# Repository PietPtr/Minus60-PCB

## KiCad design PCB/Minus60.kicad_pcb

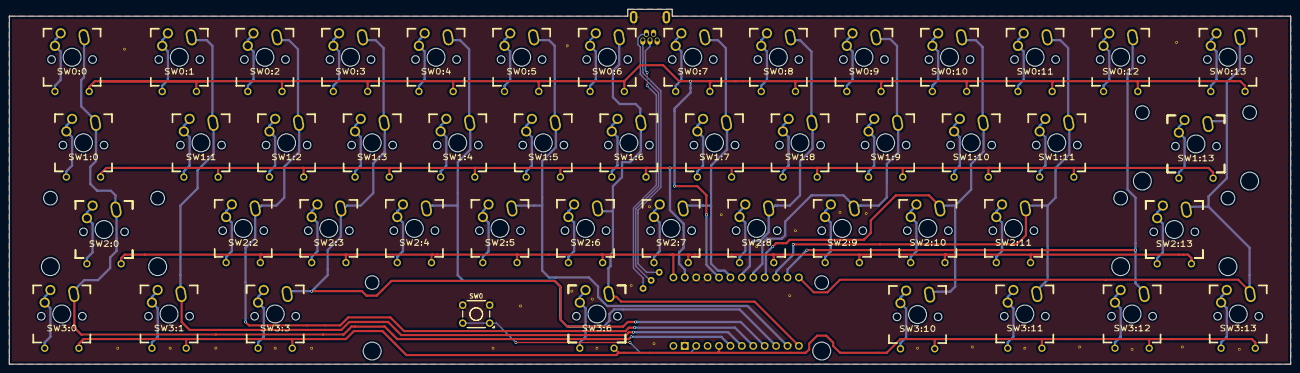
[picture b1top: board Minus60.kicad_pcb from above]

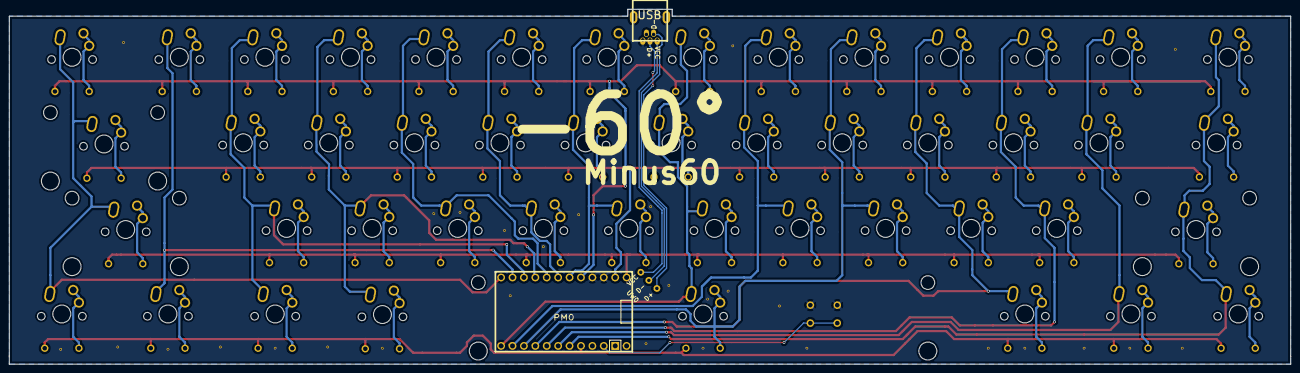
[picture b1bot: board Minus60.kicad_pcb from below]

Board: 2 copper layers, 285.2 x 79.0 mm, 51 parts (2 on the bottom side), 23 nets.

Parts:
P0: USB; USBMINI
PM0: PROMICRO
SW0: SW_PUSH; SW_TH_Tactile_Omron_B3F-10xx
SW0:0, SW0:1, SW0:2, SW0:3, SW0:4, SW0:5, SW0:6, SW0:7, SW0:8, SW0:9, SW0:10, SW0:11, SW0:12, SW0:13, SW1:0, SW1:1, SW1:2, SW1:3, SW1:4, SW1:5, SW1:6, SW1:7, SW1:8, SW1:9, SW1:10, SW1:11, SW1:13, SW2:0, SW2:2, SW2:3, SW2:4, SW2:5, SW2:6, SW2:7, SW2:8, SW2:9, SW2:10, SW2:11, SW2:13, SW3:0, SW3:1, SW3:3, SW3:6, SW3:10, SW3:11, SW3:12, SW3:13: SWITCH_DIODE; SMK_SWITCH_DIODE_1U
UW0: USBWireConnection; USBWirePins

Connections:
/COL0: PM0.17, SW0:0.1, SW1:0.1, SW2:0.1, SW3:0.1
/COL1: PM0.18, SW0:1.1, SW1:1.1, SW3:1.1
/COL2: PM0.19, SW0:2.1, SW1:2.1, SW2:2.1
/COL3: PM0.20, SW0:3.1, SW1:3.1, SW2:3.1, SW3:3.1
/COL4: PM0.21, SW0:4.1, SW1:4.1, SW2:4.1
/COL5: PM0.22, SW0:5.1, SW1:5.1, SW2:5.1
/COL6: PM0.23, SW0:6.1, SW1:6.1, SW2:6.1, SW3:6.1
/COL7: PM0.5, SW0:7.1, SW1:7.1, SW2:7.1
/COL8: PM0.6, SW0:8.1, SW1:8.1, SW2:8.1
/COL9: PM0.7, SW0:9.1, SW1:9.1, SW2:9.1
/COL10: PM0.8, SW0:10.1, SW1:10.1, SW2:10.1, SW3:10.1
/COL11: PM0.9, SW0:11.1, SW1:11.1, SW2:11.1, SW3:11.1
/COL12: PM0.10, SW0:12.1, SW3:12.1
/COL13: PM0.11, SW0:13.1, SW1:13.1, SW2:13.1, SW3:13.1
/ROW0: PM0.4, SW0:0.4, SW0:1.4, SW0:2.4, SW0:3.4, SW0:4.4, SW0:5.4, SW0:6.4, SW0:7.4, SW0:8.4, SW0:9.4, SW0:10.4, SW0:11.4, SW0:12.4, SW0:13.4
/ROW1: PM0.1, SW1:0.4, SW1:1.4, SW1:2.4, SW1:3.4, SW1:4.4, SW1:5.4, SW1:6.4, SW1:7.4, SW1:8.4, SW1:9.4, SW1:10.4, SW1:11.4, SW1:13.4
/ROW2: PM0.0, SW2:0.4, SW2:2.4, SW2:3.4, SW2:4.4, SW2:5.4, SW2:6.4, SW2:7.4, SW2:8.4, SW2:9.4, SW2:10.4, SW2:11.4, SW2:13.4
/ROW3: PM0.16, SW3:0.4, SW3:1.4, SW3:3.4, SW3:6.4, SW3:10.4, SW3:11.4, SW3:12.4, SW3:13.4
/RST: PM0.14, SW0.1
GND: P0.5, P0.6, PM0.2, PM0.3, PM0.13, SW0.2
unnamed: P0.1, UW0.1
unnamed: P0.2, UW0.2
unnamed: P0.3, UW0.3

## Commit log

2017-03-20 Add stabilizers
2017-03-20 Flip spacebar stabilizer
2017-03-20 Add logo
2017-04-09 Add actual cherry support
2017-04-09 Fix random issues
